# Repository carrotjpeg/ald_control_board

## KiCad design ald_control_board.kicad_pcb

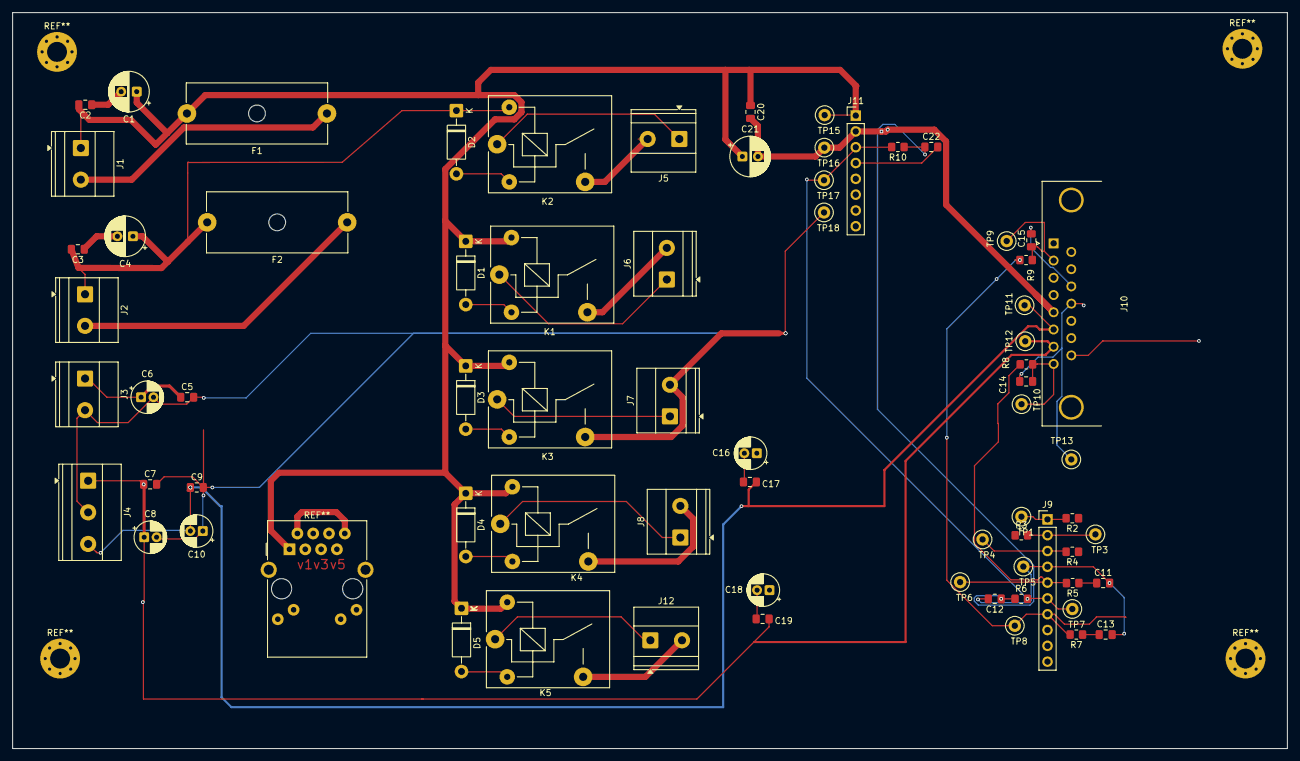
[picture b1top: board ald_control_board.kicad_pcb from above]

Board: 2 copper layers, 204.9 x 118.3 mm, 72 parts (0 on the bottom side), 30 nets.

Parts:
C1, C4, C21: 47uF; CP_Radial_D6.3mm_P2.50mm
C2, C3, C5, C7, C9, C20: 0.1uF; C_0805_2012Metric_Pad1.18x1.45mm_HandSolder
C6, C8, C10: 10uF; CP_Radial_D5.0mm_P2.00mm
C11, C12, C13, C14, C15, C22: 10nF; C_0805_2012Metric_Pad1.18x1.45mm_HandSolder
C16, C18: 10µF; CP_Radial_D5.0mm_P2.00mm
C17, C19: 0.1µF; C_0805_2012Metric_Pad1.18x1.45mm_HandSolder
D1, D2, D3, D4, D4#2: Diode; D_DO-41_SOD81_P10.16mm_Horizontal
F1, F2: Fuse; Fuseholder_Cylinder-5x20mm_Schurter_0031_8201_Horizontal_Op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
J1: PWR_24V_IN; TerminalBlock_Phoenix_MKDS-1,5-2-5.08_1x02_P5.08mm_Horizont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
J2: PWR_12V_IN; TerminalBlock_Phoenix_MKDS-1,5-2-5.08_1x02_P5.08mm_Horizont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
J3: PWR_5V_IN; TerminalBlock_Phoenix_MKDS-1,5-2-5.08_1x02_P5.08mm_Horizont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
J4: PWR_±15V_IN; TerminalBlock_Phoenix_MKDS-1,5-3-5.08_1x03_P5.08mm_Horizont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
J5: J_FORELINE_VALVE; TerminalBlock_Phoenix_MKDS-1,5-2-5.08_1x02_P5.08mm_Horizont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
J6: J_PRECURSOR_A; TerminalBlock_Phoenix_MKDS-1,5-2-5.08_1x02_P5.08mm_Horizont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
J7: J_N2_PURGE; TerminalBlock_Phoenix_MKDS-1,5-2-5.08_1x02_P5.08mm_Horizont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
J8: J_SPARE; TerminalBlock_Phoenix_MKDS-1,5-2-5.08_1x02_P5.08mm_Horizont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
J9: DAQ_IO; PinHeader_1x10_P2.54mm_Vertical
J10: MFC_DB15; DSUB-15_Socket_Horizontal_P2.77x2.84mm_EdgePinOffset4.94mm_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
J11: VACUUM_GAUGE_8PIN; PinHeader_1x08_P2.54mm_Vertical
J12: J_RELAY; TerminalBlock_Phoenix_MKDS-1,5-2-5.08_1x02_P5.08mm_Horizont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
K1: Relay 2; Relay_SPST_SANYOU_SRD_Series_Form_A
K2: Relay 1; Relay_SPST_SANYOU_SRD_Series_Form_A
K3: Relay 3; Relay_SPST_SANYOU_SRD_Series_Form_A
K4: Relay 4; Relay_SPST_SANYOU_SRD_Series_Form_A
K5: Relay 5; Relay_SPST_SANYOU_SRD_Series_Form_A
R2, R3, R4: 330R; R_0805_2012Metric_Pad1.20x1.40mm_HandSolder
R5: 100R; R_0805_2012Metric_Pad1.20x1.40mm_HandSolder
R6, R7, R10: 1k; R_0805_2012Metric_Pad1.20x1.40mm_HandSolder
R8, R9: 1kΩ; R_0805_2012Metric_Pad1.20x1.40mm_HandSolder
R_GND_TIE1: R1; NetTie-2_SMD_Pad0.5mm
TP1, TP3, TP4, TP5, TP6, TP7, TP8, TP9, TP10, TP11, TP12, TP13: TestPoint; TestPoint_Loop_D2.50mm_Drill1.0mm
TP15: TP_VAC_24V; TestPoint_Loop_D2.50mm_Drill1.0mm
TP16: TP_VAC_GND; TestPoint_Loop_D2.50mm_Drill1.0mm
TP17: TP_VAC_SIG; TestPoint_Loop_D2.50mm_Drill1.0mm
TP18: TP_VAC_SIG_GND; TestPoint_Loop_D2.50mm_Drill1.0mm

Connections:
+5V: C5.1, C6.1, J3.1
+12V: C3.2, C4.1, D2.1 (K), F2.2, J2.1, K2.5
+15V: C7.1, C8.1, C19.2, J4.1, J10.7, TP12.1
+24V: C1.1, C2.2, C20.1, C21.1, D1.1 (K), D3.1 (K), D4.1 (K), D4#2.1 (K), F1.2, J1.1, J11.1, K1.5, K3.5, K4.5, K5.5, TP15.1
-15V: C9.1, C10.2, C17.2, J4.3, J10.6, TP11.1
/daq_interface/AI_MFC_FLOW: J9.7, R7.2, R9.1, TP8.1
/daq_interface/AI_MFC_FLOW_FILT: C13.1, R7.1
/daq_interface/AO_MFC_SETPOINT: J9.5, R5.2, R8.1, TP6.1
/daq_interface/AO_MFC_SP_FILT: C11.1, R5.1
/daq_interface/DO_FORELINE: J9.1, R2.2, TP1.1
/daq_interface/DO_N2: J9.3, R4.2, TP4.1
/daq_interface/DO_PRECURSOR: J9.2, R3.2, TP3.1
/relay_board/P0.0: D2.2 (A), K2.2
/relay_board/P0.1: D1.2 (A), K1.2
/relay_board/P0.2: D3.2 (A), K3.P0.2
/relay_board/P0.3: D4.2 (A), K4.2
/vacuum_gauge_interface/AI_PRESSURE: J9.6, J11.3, R6.2, R10.2, TP7.1, TP17.1
/vacuum_gauge_interface/AI_PRESSURE_FILT: C12.1, C22.1, R6.1, R10.1
GND_PWR: C1.2, C2.1, C3.1, C4.2, C16.1, C18.1, C20.2, C21.2, F1.1, F2.1, J1.2, J2.2, J5.2, J6.2, J7.2, J8.2, J10.5, J11.2, J12.2, K1.3, K2.3, K3.3, K4.3, K5.3, R_GND_TIE1.1, TP16.1
GND_SIG: C5.2, C6.2, C7.2, C8.2, C9.2, C10.1, C11.2, C12.2, C13.2, C14.2, C15.2, C22.2, J3.2, J4.2, J9.4, J9.8, J10.11 (P111), J10.12, J11.4, R_GND_TIE1.2, TP5.1, TP13.1, TP18.1
unnamed: C14.1, J10.8, R8.2, TP10.1
unnamed: C15.1, J10.2, R9.2, TP9.1
unnamed: C16.2, C17.1
unnamed: C18.2, C19.1
unnamed: J5.1, K2.1
unnamed: J6.1, K1.1
unnamed: J7.1, K3.1
unnamed: J8.1, K4.1
unnamed: J12.1, K5.1
PO.4: D4#2.2 (A), K5.2

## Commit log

2026-01-11 Add power input schematic with split grounds and decoupling
2026-01-11 Add full KiCad project files
2026-01-11 Add relay board schematic
2026-01-11 fix ERC errors in relay board schematic
2026-01-11 complete daq interface with digital buffering and analog filtering
2026-01-12 complete mfc interface
2026-01-12 fixed GND and diodes on the relay board
2026-01-12 minor cleanup to power input schematic
2026-01-12 add documentation and updates
2026-01-12 add vacuum gauge interface with analog filtering and test points
2026-01-13 Updated the relay board schematic
2026-01-13 Clean up duplicates in schematic components
2026-01-13 Clean up duplicates in schematic components and assign footprints
2026-01-13 Finished component placement and layout is ready for routing
2026-01-14 im so happy
2026-01-15 Hopefully finalized PCB design and other files
2026-01-15 Fix: move fabrication files to Gerbers folder
2026-01-15 rotated MFC and 10 pin daq
2026-01-15 hopefully finalized pcb
2026-01-15 5 relays
2026-01-21 added cat 5 and fixed some b.cu traces for -15v
